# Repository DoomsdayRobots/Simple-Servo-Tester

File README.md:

# Simple-Servo-Tester
As the name implies, it's a simple servo tester...

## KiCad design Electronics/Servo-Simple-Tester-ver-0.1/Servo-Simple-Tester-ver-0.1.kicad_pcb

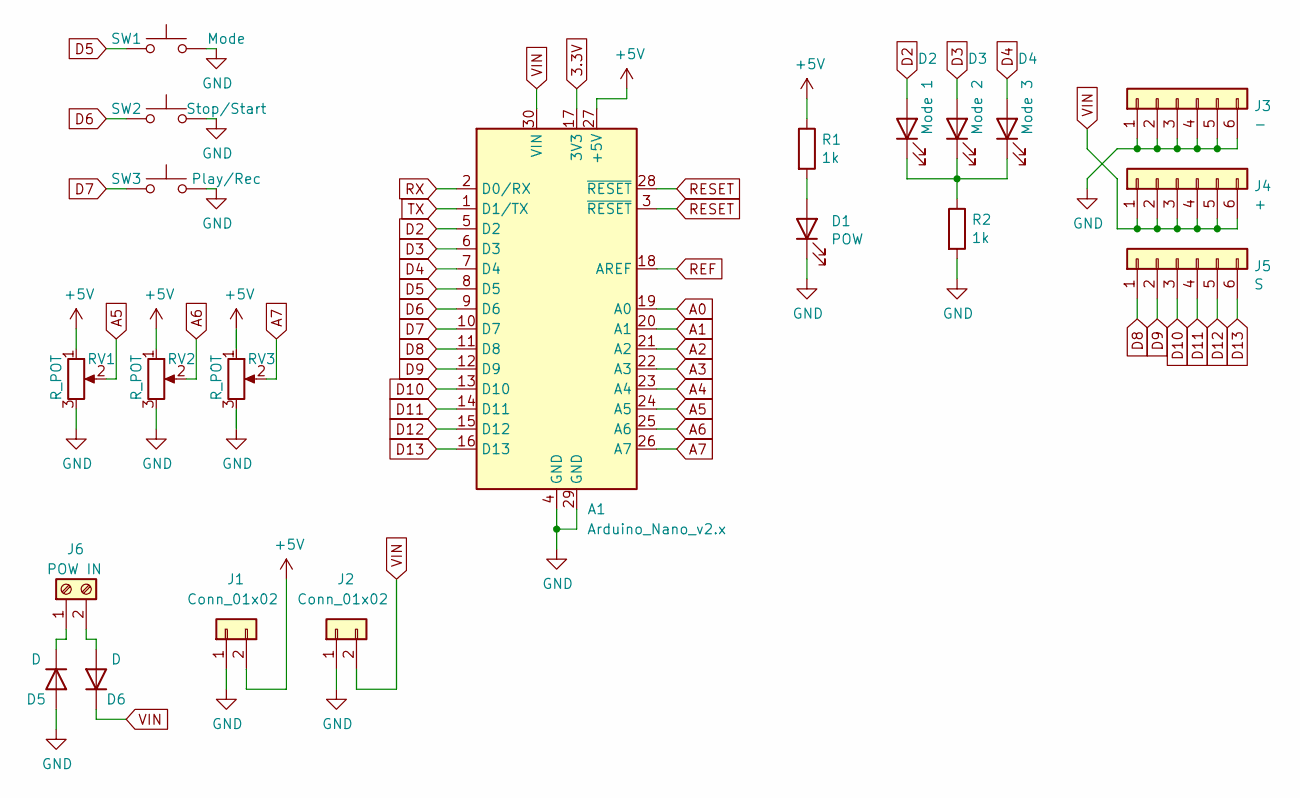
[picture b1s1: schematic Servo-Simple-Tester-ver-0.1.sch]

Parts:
A1: Arduino_Nano_v2.x; Arduino_Nano
D1: POW; LED_D3.0mm
D2: Mode 1; LED_D3.0mm
D3: Mode 2; LED_D3.0mm
D4: Mode 3; LED_D3.0mm
D5, D6: D; D_A-405_P7.62mm_Horizontal
J1, J2: Conn_01x02; PinHeader_1x02_P2.54mm_Vertical
J3: -; conn_01x06
J4: +; conn_01x06
J5: S; conn_01x06
J6: POW IN; TerminalBlock_4Ucon_1x02_P3.50mm_Vertical
R1, R2: 1k; R_Axial_DIN0204_L3.6mm_D1.6mm_P7.62mm_Horizontal
RV1, RV2, RV3: R_POT; Potentiometer_Alpha_RD902F-40-00D_Dual_Vertical
SW1: Mode; SW_PUSH_6mm
SW2: Stop/Start; SW_PUSH_6mm
SW3: Play/Rec; SW_PUSH_6mm

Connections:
3.3V: A1.17 (3V3)
+5V: A1.27 (+5V), J1.2, R1.1, RV1.1, RV2.1, RV3.1
A0: A1.19 (A0)
A1: A1.20 (A1)
A2: A1.21 (A2)
A3: A1.22 (A3)
A4: A1.23 (A4)
A5: A1.24 (A5), RV1.2
A6: A1.25 (A6), RV2.2
A7: A1.26 (A7), RV3.2
D2: A1.5 (D2), D2.2 (A)
D3: A1.6 (D3), D3.2 (A)
D4: A1.7 (D4), D4.2 (A)
D5: A1.8 (D5), SW1.1
D6: A1.9 (D6), SW2.1
D7: A1.10 (D7), SW3.1
D8: A1.11 (D8), J5.1
D9: A1.12 (D9), J5.2
D10: A1.13 (D10), J5.3
D11: A1.14 (D11), J5.4
D12: A1.15 (D12), J5.5
D13: A1.16 (D13), J5.6
GND: A1.4 (GND), A1.29 (GND), D1.1 (K), D5.2 (A), J1.1, J2.1, J3.1, J3.2, J3.3, J3.4, J3.5, J3.6, R2.2, RV1.3, RV2.3, RV3.3, SW1.2, SW2.2, SW3.2
unnamed: D1.2 (A), R1.2
unnamed: D2.1 (K), D3.1 (K), D4.1 (K), R2.1
unnamed: D5.1 (K), J6.1
unnamed: D6.2 (A), J6.2
REF: A1.18 (AREF)
RESET: A1.3 (~RESET), A1.28 (~RESET)
RX: A1.2 (D0/RX)
TX: A1.1 (D1/TX)
VIN: A1.30 (VIN), D6.1 (K), J2.2, J4.1, J4.2, J4.3, J4.4, J4.5, J4.6

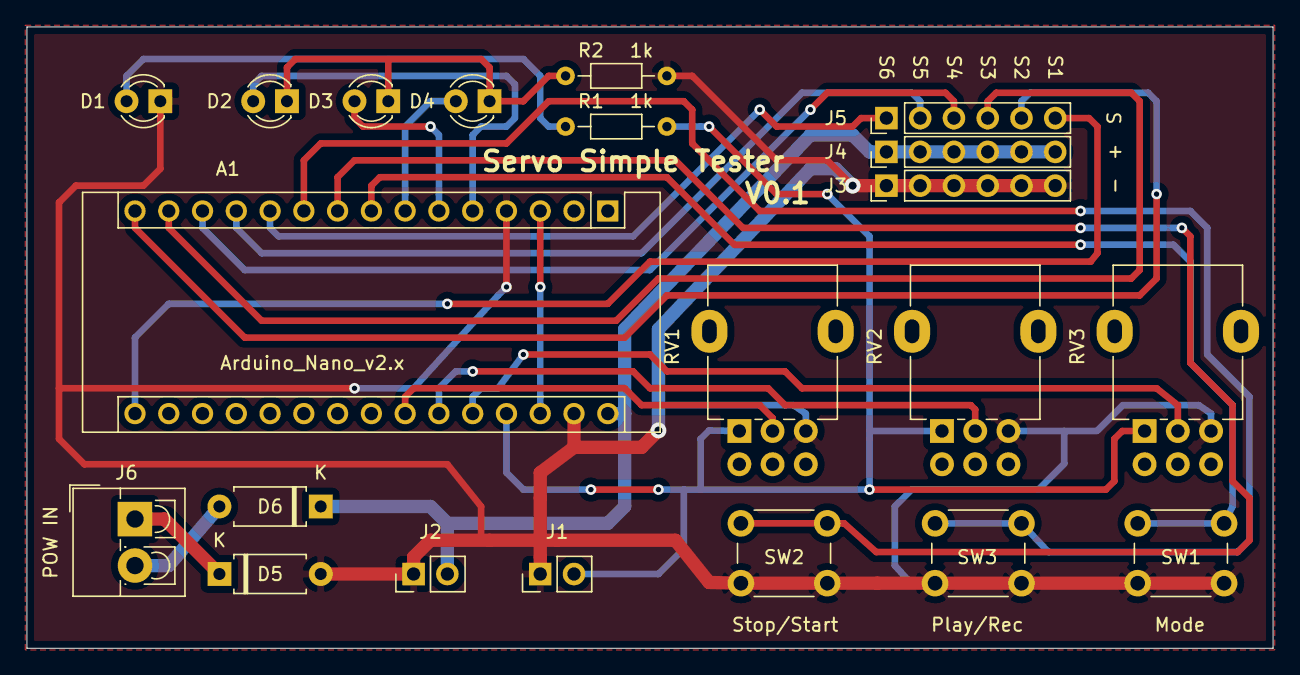
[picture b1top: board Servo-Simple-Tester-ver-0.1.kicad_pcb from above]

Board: 2 copper layers, 93.7 x 46.7 mm, 21 parts (0 on the bottom side), 23 nets.
